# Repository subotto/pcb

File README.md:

# pcb
Progetto in EAGLE-EAD per la scheda integrata
situazione (26/04/15)

Il repo contiene tre progetti Eagle (la versione freeware non mi consente di riunirli in uno solo, per ora)
- power_board: è la scheda di alimenazione PoE, già stampata e realizzata. L'abbiamo usata l'ultima volta.
- sub_081 / 082: sono gli schemi per i nuovi circuiti delle fotocellule ideati da Francesco Hoch e sviluppati da lui e me. Lo schema 081 implementa l'amplificatore / comparatore con due opamp (TL081), lo schema 082 li riunisce in un singolo integrato (TL082) per economia di spazio e di costi. Prima della 24ore lo schema è stato testato con successo su breadboard (con due uA741, perché quello avevamo), ma non ho fatto in tempo a finire di diseagnare e realizzare la scheda completa e dunque abbiamo ripiegato su quelle di Guatieri, come ben ricordate.

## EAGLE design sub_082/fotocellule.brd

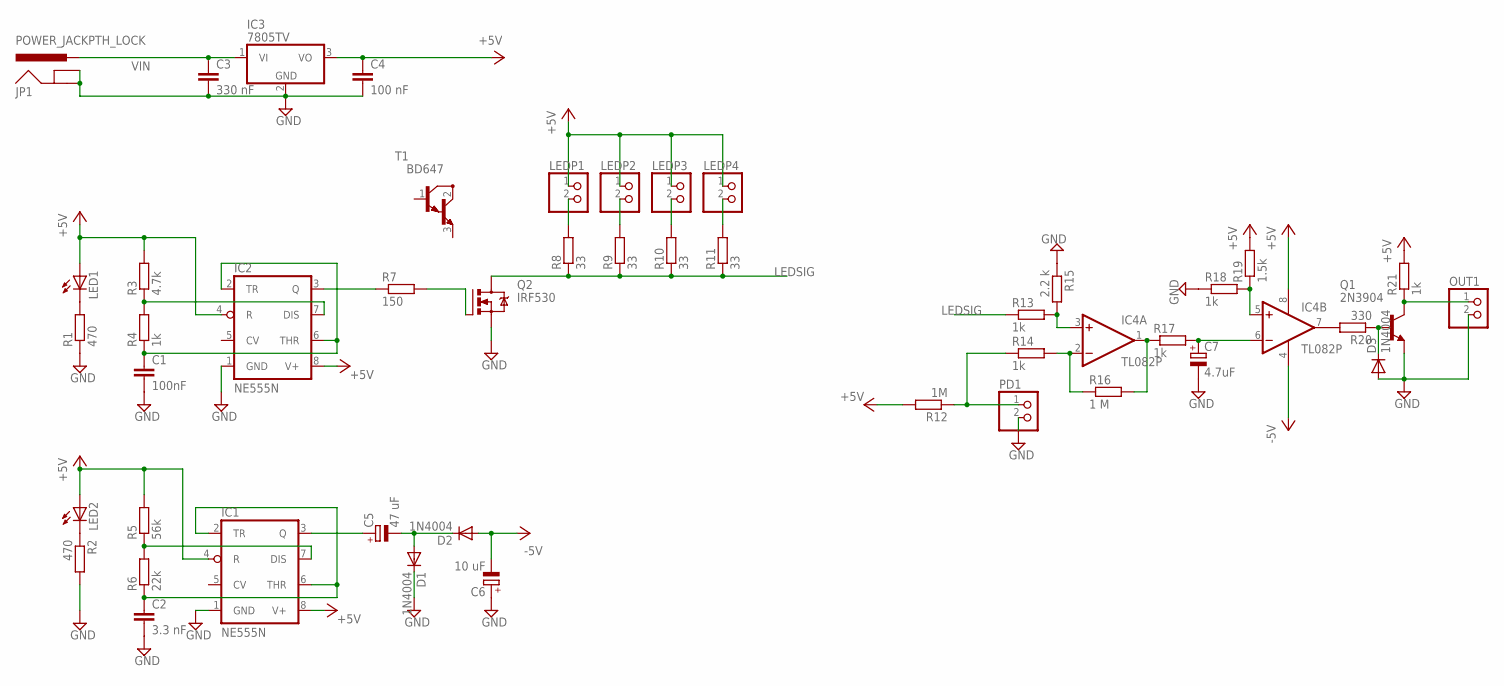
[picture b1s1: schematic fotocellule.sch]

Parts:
C1: 100nF; C025-024X044
C2: 3.3 nF; C025-024X044
C3: 330 nF; C025-024X044
C4: 100 nF; C025-024X044
C5: 47 uF; E2,5-5
C6: 10 uF; E2,5-5
C7: 4.7uF; E2,5-6
D1, D2, D3: 1N4004; DO41-10
IC1, IC2: NE555N; DIL08
IC3: 7805TV; TO220V
IC4: TL082P; DIL08
JP1: POWER_JACKPTH_LOCK; POWER_JACK_PTH_LOCK
LED1, LED2: LED5MM
LEDP1, LEDP2, LEDP3, LEDP4: PINHD-1X2; 1X02
OUT1: PINHD-1X2; 1X02
PD1: PINHD-1X2; 1X02
Q1: 2N3904; TO92
Q2: IRF530; TO220BV
R1, R2: 470; 0207/10
R3: 4.7k; 0207/10
R4, R13, R14, R17, R18, R21: 1k; 0207/10
R5: 56k; 0207/10
R6: 22k; 0207/10
R7: 150; 0207/10
R8, R9, R10, R11: 33; 0207/10
R12: 1M; 0207/10
R15: 2.2 k; 0207/10
R16: 1 M; 0207/10
R19: 1.5k; 0207/10
R20: 330; 0207/10
T1: BD647; TO220

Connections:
+5V: C4.1, IC1.4 (R), IC1.8 (V+), IC2.4 (R), IC2.8 (V+), IC3.3 (VO), IC4.8 (V+), LED1.A, LED2.A, LEDP1.1, LEDP2.1, LEDP3.1, LEDP4.1, R3.2, R5.2, R12.2, R19.2, R21.2
-5V: C6.-, D2.A, IC4.4 (V-)
GND: C1.2, C2.2, C3.2, C4.2, C6.+, C7.-, D1.C, D3.A, IC1.1 (GND), IC2.1 (GND), IC3.2 (GND), JP1.GND, JP1.GNDBREAK, OUT1.2, PD1.2, Q1.3 (E), Q2.S, R1.1, R2.2, R15.1, R18.1
LEDSIG: Q2.D, R8.1, R9.1, R10.1, R11.1, R13.1
unnamed: C1.1, IC2.2 (TR), IC2.6 (THR), R4.1
unnamed: IC2.7 (DIS), R3.1, R4.2
unnamed: IC4.3 (+IN), R13.2, R15.2
unnamed: IC4.1 (OUT), R16.2, R17.1
unnamed: C7.+, IC4.6 (-IN), R17.2
unnamed: IC4.5 (+IN), R18.2, R19.1
unnamed: C2.1, IC1.2 (TR), IC1.6 (THR), R6.1
unnamed: IC1.7 (DIS), R5.1, R6.2
unnamed: IC2.3 (Q), R7.1
unnamed: C5.+, IC1.3 (Q)
unnamed: C5.-, D1.A, D2.C
unnamed: Q2.G, R7.2
unnamed: IC4.7 (OUT), R20.2
unnamed: LED1.K (C), R1.2
unnamed: LEDP1.2, R8.2
unnamed: OUT1.1, Q1.1 (C), R21.1
unnamed: LEDP2.2, R9.2
unnamed: D3.C, Q1.2 (B), R20.1
unnamed: LEDP3.2, R10.2
unnamed: LEDP4.2, R11.2
unnamed: IC4.2 (-IN), R14.2, R16.1
unnamed: PD1.1, R12.1, R14.1
unnamed: LED2.K (C), R2.1
VIN: C3.1, IC3.1 (VI), JP1.PWR

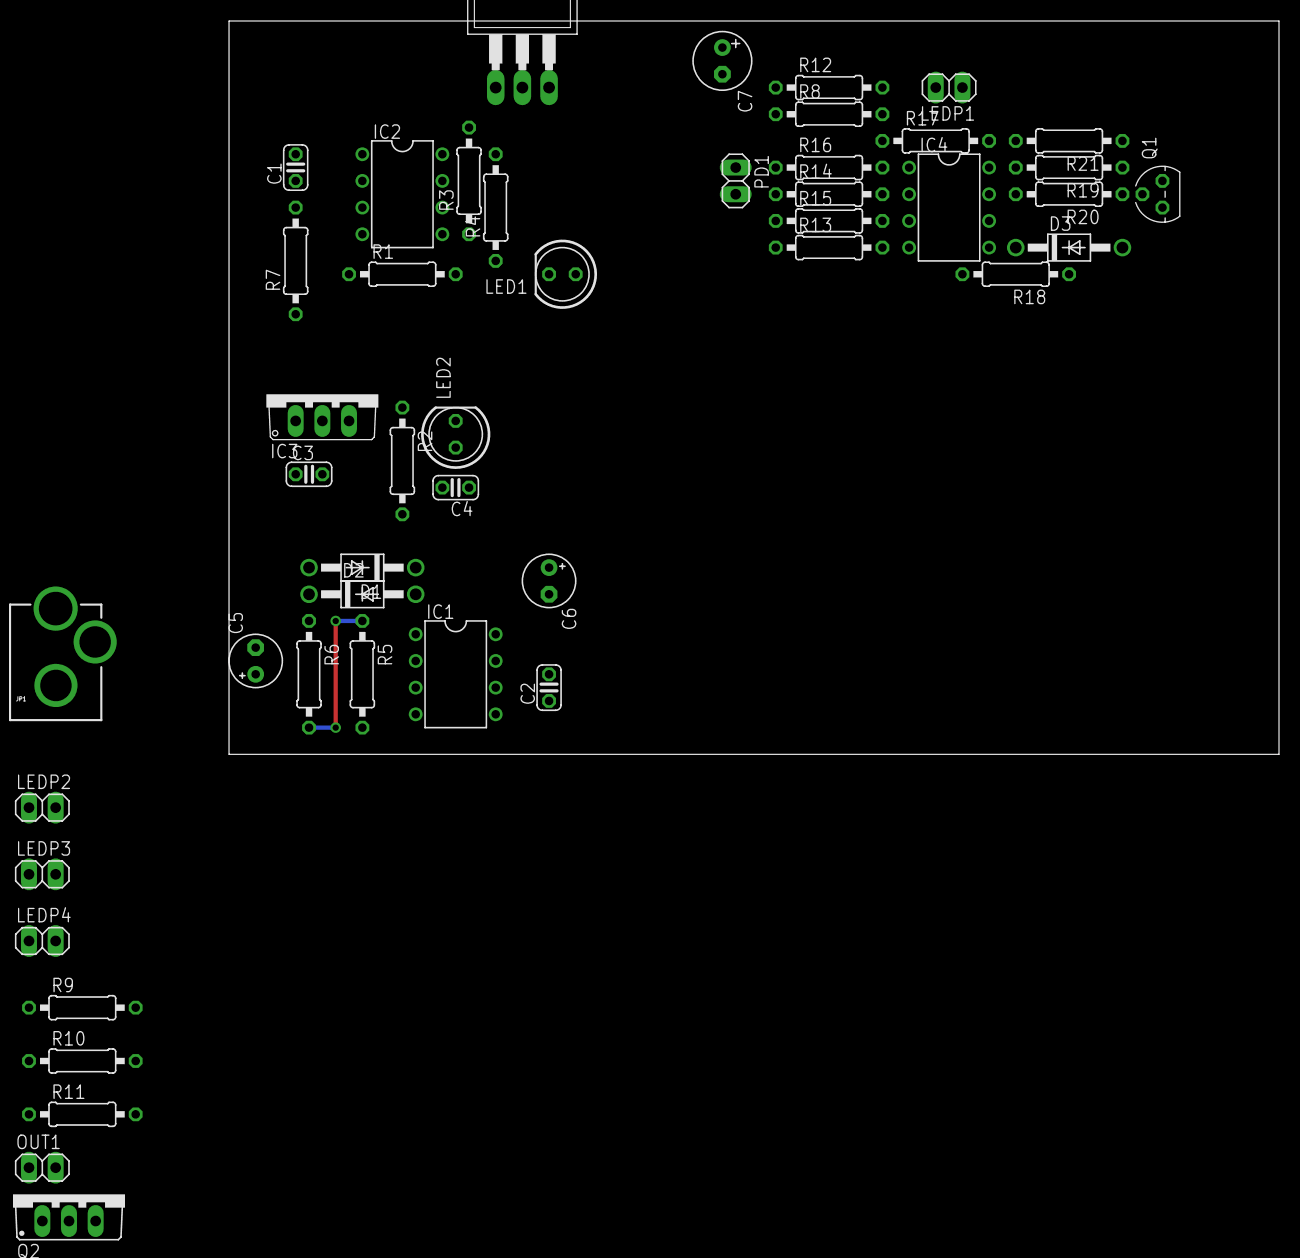
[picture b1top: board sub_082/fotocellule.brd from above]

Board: 2 copper layers, 100.0 x 69.8 mm, 47 parts (0 on the bottom side), 28 nets.

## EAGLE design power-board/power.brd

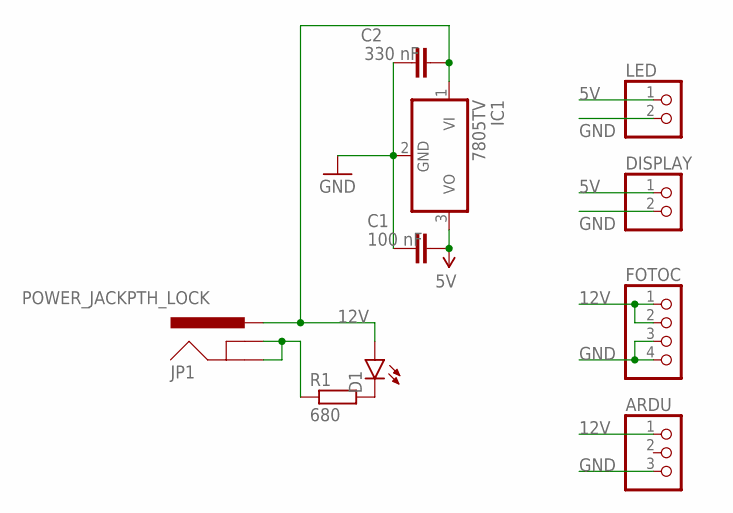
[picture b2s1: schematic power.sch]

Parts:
ARDU: PINHD-1X3; 1X03
C1: 100 nF; C025-025X050
C2: 330 nF; C025-025X050
D1: LED5MM
DISPLAY: PINHD-1X2; 1X02
FOTOC: PINHD-1X4; 1X04
IC1: 7805TV; TO220V
JP1: POWER_JACKPTH_LOCK; POWER_JACK_PTH_LOCK
LED: PINHD-1X2; 1X02
R1: 680; 0207/10

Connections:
5V: C1.1, DISPLAY.1, IC1.3 (VO), LED.1
12V: ARDU.1, C2.2, D1.A, FOTOC.1, FOTOC.2, IC1.1 (VI), JP1.PWR
GND: ARDU.3, C1.2, C2.1, DISPLAY.2, FOTOC.3, FOTOC.4, IC1.2 (GND), JP1.GND, JP1.GNDBREAK, LED.2, R1.1
unnamed: D1.K (C), R1.2

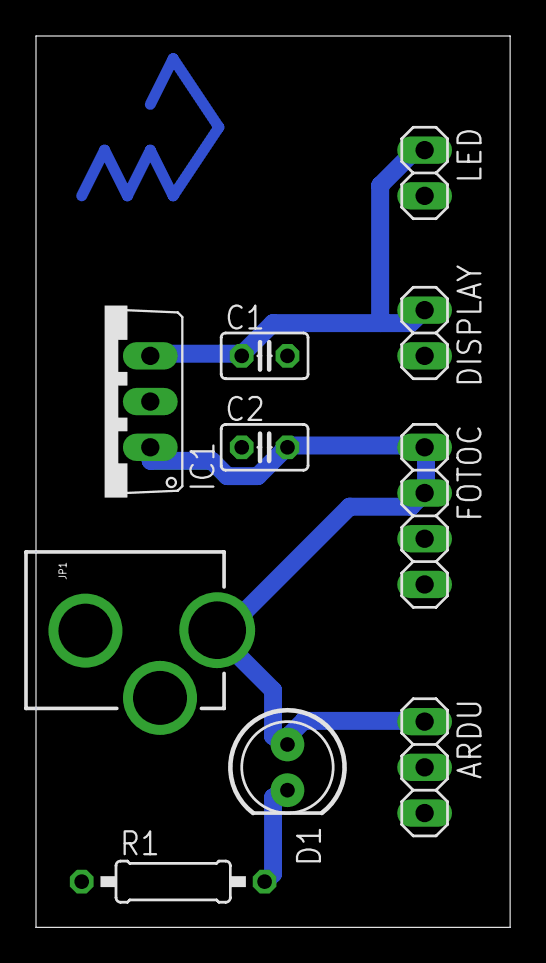
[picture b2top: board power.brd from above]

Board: 2 copper layers, 26.3 x 49.5 mm, 10 parts (0 on the bottom side), 4 nets.

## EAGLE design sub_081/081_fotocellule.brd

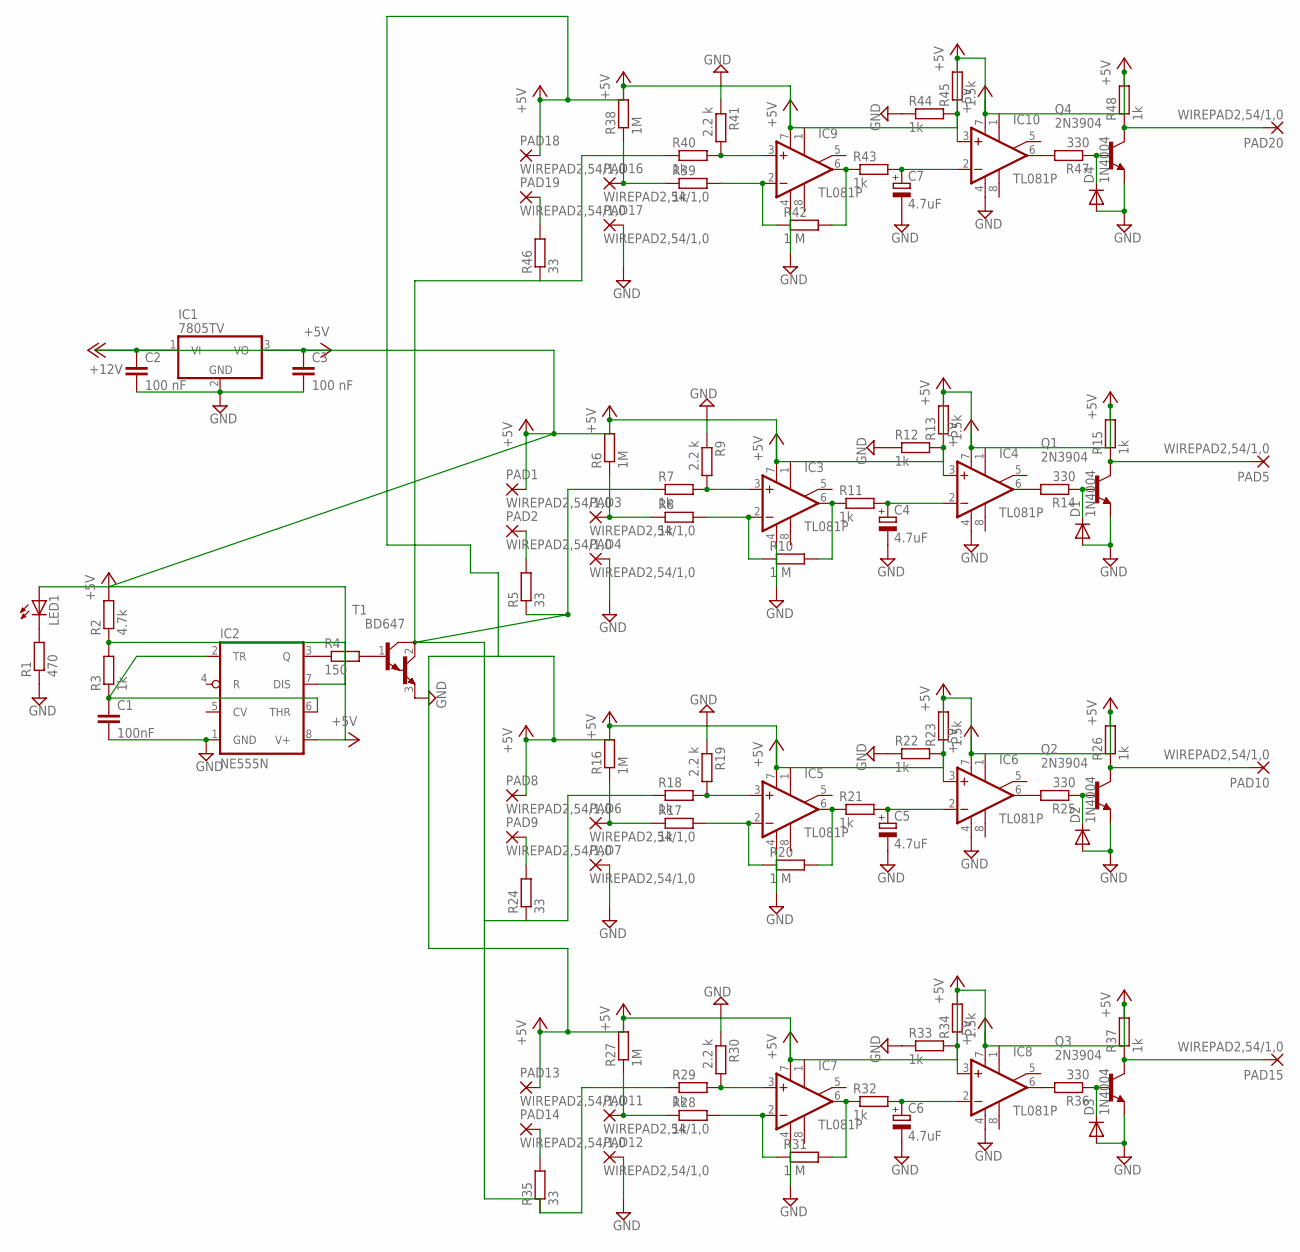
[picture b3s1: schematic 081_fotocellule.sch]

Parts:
C1: 100nF; C025-024X044
C2, C3: 100 nF; C025-024X044
C4, C5, C6, C7: 4.7uF; E2,5-6
D1, D2, D3, D4: 1N4004; DO41-10
IC1: 7805TV; TO220V
IC2: NE555N; DIL08
IC3, IC4, IC5, IC6, IC7, IC8, IC9, IC10: TL081P; DIL08
LED1: LED5MM
PAD1, PAD2, PAD3, PAD4, PAD5, PAD6, PAD7, PAD8, PAD9, PAD10, PAD11, PAD12, PAD13, PAD14, PAD15, PAD16, PAD17, PAD18, PAD19, PAD20: WIREPAD2,54/1,0; 2,54/1,0
Q1, Q2, Q3, Q4: 2N3904; TO92
R1: 470; 0207/10
R2: 4.7k; 0207/10
R3, R7, R8, R11, R12, R15, R17, R18, R21, R22, R26, R28, R29, R32, R33, R37, R39, R40, R43, R44, R48: 1k; 0207/10
R4: 150; 0207/10
R5, R24, R35, R46: 33; 0207/10
R6, R16, R27, R38: 1M; 0207/10
R9, R19, R30, R41: 2.2 k; 0207/10
R10, R20, R31, R42: 1 M; 0207/10
R13, R23, R34, R45: 1.5k; 0207/10
R14, R25, R36, R47: 330; 0207/10
T1: BD647; TO220

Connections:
+5V: C3.1, IC1.3 (VO), IC2.8 (V+), IC3.7 (V+), IC4.7 (V+), IC5.7 (V+), IC6.7 (V+), IC7.7 (V+), IC8.7 (V+), IC9.7 (V+), IC10.7 (V+), LED1.A, PAD1.1, PAD8.1, PAD13.1, PAD18.1, R2.2, R6.2, R13.2, R15.2, R16.2, R23.2, R26.2, R27.2, R34.2, R37.2, R38.2, R45.2, R48.2
GND: C1.2, C2.2, C3.2, C4.-, C5.-, C6.-, C7.-, D1.A, D2.A, D3.A, D4.A, IC1.2 (GND), IC2.1 (GND), IC3.4 (V-), IC4.4 (V-), IC5.4 (V-), IC6.4 (V-), IC7.4 (V-), IC8.4 (V-), IC9.4 (V-), IC10.4 (V-), PAD4.1, PAD7.1, PAD12.1, PAD17.1, Q1.3 (E), Q2.3 (E), Q3.3 (E), Q4.3 (E), R1.1, R9.1, R12.1, R19.1, R22.1, R30.1, R33.1, R41.1, R44.1, T1.3 (E)
unnamed: PAD3.1, R6.1, R8.1
unnamed: IC3.2 (-IN), R8.2, R10.1
unnamed: IC3.3 (+IN), R7.2, R9.2
unnamed: IC3.6 (OUT), R10.2, R11.1
unnamed: C4.+, IC4.2 (-IN), R11.2
unnamed: IC4.3 (+IN), R12.2, R13.1
unnamed: PAD2.1, R5.2
unnamed: PAD6.1, R16.1, R17.1
unnamed: IC2.3 (Q), R4.1
unnamed: C1.1, IC2.2 (TR), IC2.6 (THR), R3.1
unnamed: IC4.6 (OUT), R14.2
unnamed: R4.2, T1.1 (B)
unnamed: IC5.2 (-IN), R17.2, R20.1
unnamed: LED1.K (C), R1.2
unnamed: IC2.7 (DIS), R2.1, R3.2
unnamed: PAD5.1, Q1.1 (C), R15.1
unnamed: IC5.3 (+IN), R18.2, R19.2
unnamed: D1.C, Q1.2 (B), R14.1
unnamed: IC5.6 (OUT), R20.2, R21.1
unnamed: C5.+, IC6.2 (-IN), R21.2
unnamed: IC6.3 (+IN), R22.2, R23.1
unnamed: PAD9.1, R24.2
unnamed: PAD10.1, Q2.1 (C), R26.1
unnamed: D2.C, Q2.2 (B), R25.1
unnamed: IC6.6 (OUT), R25.2
unnamed: PAD11.1, R27.1, R28.1
unnamed: IC7.2 (-IN), R28.2, R31.1
unnamed: IC7.3 (+IN), R29.2, R30.2
unnamed: IC7.6 (OUT), R31.2, R32.1
unnamed: C6.+, IC8.2 (-IN), R32.2
unnamed: IC8.3 (+IN), R33.2, R34.1
unnamed: PAD14.1, R35.2
unnamed: PAD15.1, Q3.1 (C), R37.1
unnamed: D3.C, Q3.2 (B), R36.1
unnamed: IC8.6 (OUT), R36.2
unnamed: PAD16.1, R38.1, R39.1
unnamed: IC9.2 (-IN), R39.2, R42.1
unnamed: IC9.3 (+IN), R40.2, R41.2
unnamed: IC9.6 (OUT), R42.2, R43.1
unnamed: C7.+, IC10.2 (-IN), R43.2
unnamed: IC10.3 (+IN), R44.2, R45.1
unnamed: PAD19.1, R46.2
unnamed: R5.1, R7.1, R18.1, R24.1, R29.1, R35.1, R40.1, R46.1, T1.2 (C)
unnamed: PAD20.1, Q4.1 (C), R48.1
unnamed: D4.C, Q4.2 (B), R47.1
unnamed: IC10.6 (OUT), R47.2
VCC: C2.1, IC1.1 (VI)

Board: 2 copper layers, 95 parts (0 on the bottom side), 49 nets, no tracks yet.

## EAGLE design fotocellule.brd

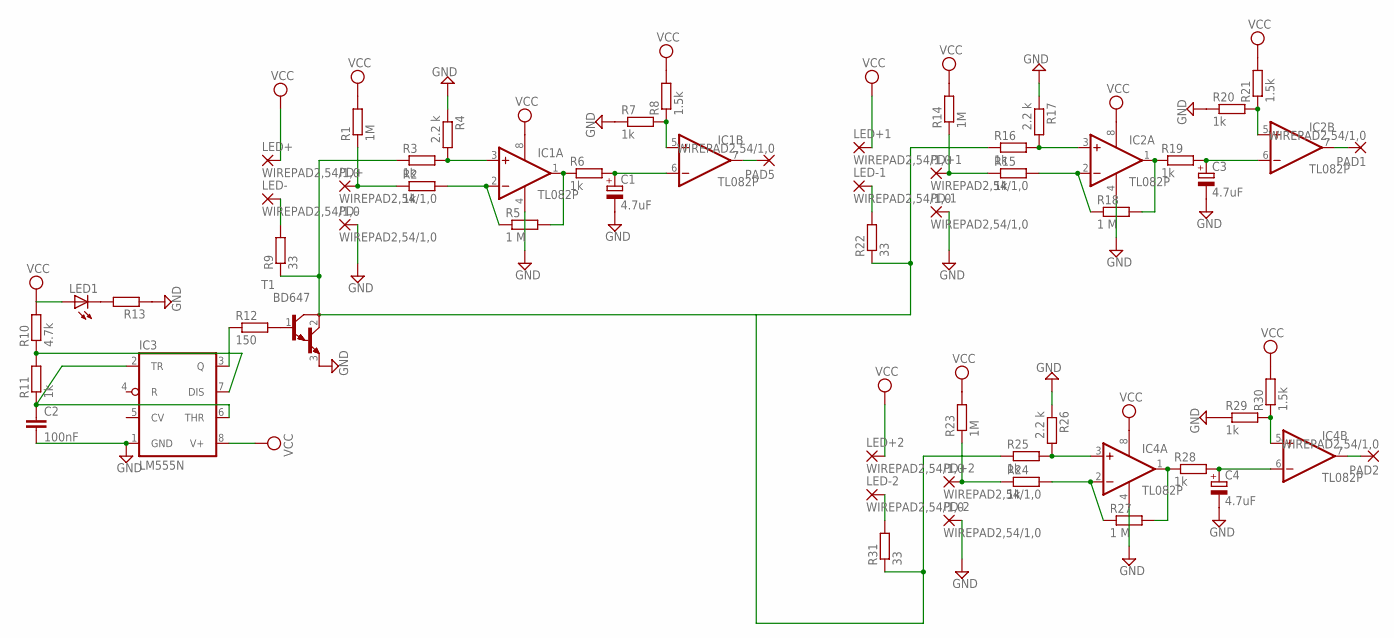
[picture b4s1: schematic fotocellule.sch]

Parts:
C1, C3, C4: 4.7uF; E2,5-6
C2: 100nF; C025-024X044
IC1, IC2, IC4: TL082P; DIL08
IC3: LM555N; DIL08
LED1: LED5MM
LED+, LED+1, LED+2: WIREPAD2,54/1,0; 2,54/1,0
LED-, LED-1, LED-2: WIREPAD2,54/1,0; 2,54/1,0
PAD1, PAD2, PAD5: WIREPAD2,54/1,0; 2,54/1,0
PD+, PD+1, PD+2: WIREPAD2,54/1,0; 2,54/1,0
PD-, PD-1, PD-2: WIREPAD2,54/1,0; 2,54/1,0
R1, R14, R23: 1M; 0207/10
R2, R3, R6, R7, R11, R15, R16, R19, R20, R24, R25, R28, R29: 1k; 0207/10
R4, R17, R26: 2.2 k; 0207/10
R5, R18, R27: 1 M; 0207/10
R8, R21, R30: 1.5k; 0207/10
R9, R22, R31: 33; 0207/10
R10: 4.7k; 0207/10
R12: 150; 0207/10
R13: R-EU_0207/10; 0207/10
T1: BD647; TO220

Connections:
GND: C1.-, C2.2, C3.-, C4.-, IC1.4 (V-), IC2.4 (V-), IC3.1 (GND), IC4.4 (V-), PD-.1, PD-1.1, PD-2.1, R4.1, R7.1, R13.1, R17.1, R20.1, R26.1, R29.1, T1.3 (E)
unnamed: PD+.1, R1.1, R2.1
unnamed: IC1.2 (-IN), R2.2, R5.1
unnamed: IC1.3 (+IN), R3.2, R4.2
unnamed: IC1.1 (OUT), R5.2, R6.1
unnamed: C1.+, IC1.6 (-IN), R6.2
unnamed: IC1.5 (+IN), R7.2, R8.1
unnamed: LED-.1, R9.2
unnamed: IC3.3 (Q), R12.1
unnamed: C2.1, IC3.2 (TR), IC3.6 (THR), R11.1
unnamed: IC3.7 (DIS), R10.1, R11.2
unnamed: R12.2, T1.1 (B)
unnamed: IC1.7 (OUT), PAD5.1
unnamed: LED1.K (C), R13.2
unnamed: PD+1.1, R14.1, R15.1
unnamed: IC2.2 (-IN), R15.2, R18.1
unnamed: IC2.3 (+IN), R16.2, R17.2
unnamed: IC2.1 (OUT), R18.2, R19.1
unnamed: C3.+, IC2.6 (-IN), R19.2
unnamed: IC2.5 (+IN), R20.2, R21.1
unnamed: LED-1.1, R22.2
unnamed: R3.1, R9.1, R16.1, R22.1, R25.1, R31.1, T1.2 (C)
unnamed: IC2.7 (OUT), PAD1.1
unnamed: PD+2.1, R23.1, R24.1
unnamed: IC4.2 (-IN), R24.2, R27.1
unnamed: IC4.3 (+IN), R25.2, R26.2
unnamed: IC4.1 (OUT), R27.2, R28.1
unnamed: C4.+, IC4.6 (-IN), R28.2
unnamed: IC4.5 (+IN), R29.2, R30.1
unnamed: LED-2.1, R31.2
unnamed: IC4.7 (OUT), PAD2.1
VCC: IC1.8 (V+), IC2.8 (V+), IC3.8 (V+), IC4.8 (V+), LED1.A, LED+.1, LED+1.1, LED+2.1, R1.2, R8.2, R10.2, R14.2, R21.2, R23.2, R30.2

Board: 2 copper layers, 56 parts (0 on the bottom side), 32 nets, no tracks yet.

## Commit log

2015-02-14 First commit: scheda fotocellule con TL082
2015-02-16 Risistemati i due progetti per l'utilizzo dei singoli/doppi opamp
2015-02-17 Power board added
2015-02-17 power board ok
2015-02-17 Power board printed
2015-02-21 Learned how to use net (instead of wires) cleaned connections in schematic made ground plane a real GND routed like a boss \m/
2015-02-21 .gitignore is now working
2015-02-21 modificato gitignore per i file di eagle
2015-02-21 Sync .epf files
2015-02-21 Rewired correctly sub082
2015-04-26 Aggiornato README
2015-04-26 Aggiornato README al 26/04
2015-04-26 Aggiornato README
    mi spiegate come si formatta questo file?

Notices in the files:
parts and their libraries:
SparkFun-Connectors: Licensing: Creative Commons ShareAlike 4.0 International - https://creativecommons.org/licenses/by-sa/4.0
